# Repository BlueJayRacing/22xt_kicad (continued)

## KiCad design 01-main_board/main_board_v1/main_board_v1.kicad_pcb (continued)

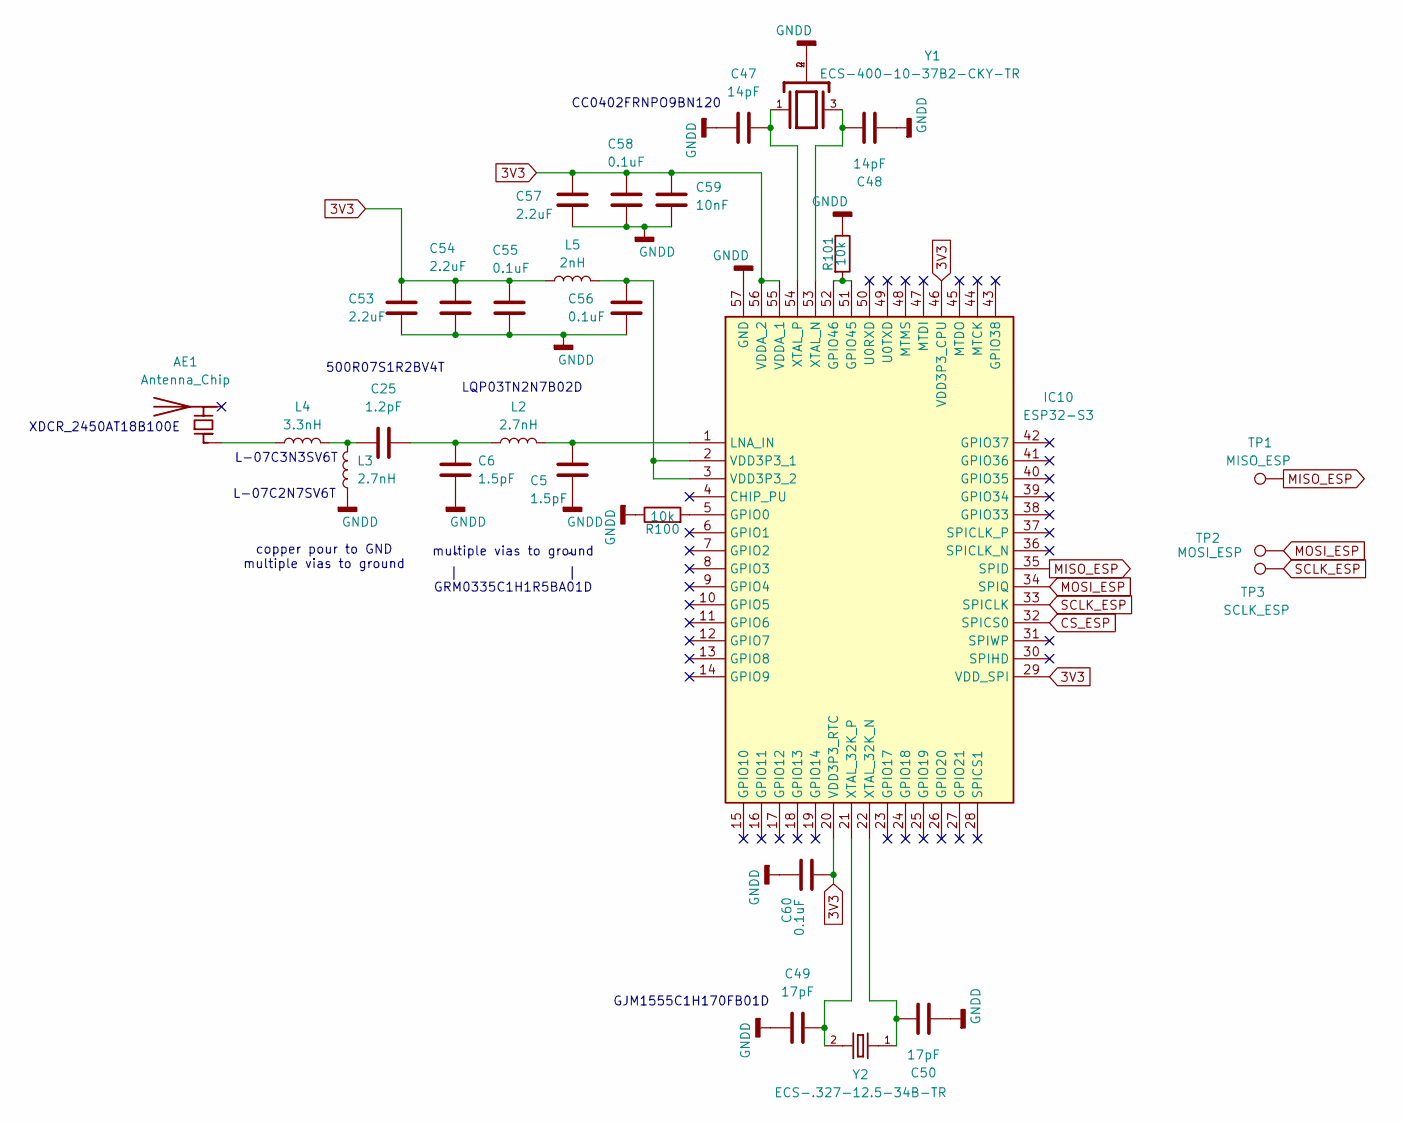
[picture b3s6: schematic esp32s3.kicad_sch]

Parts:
AE1: Antenna_Chip; XDCR_2450AT18B100E
C5, C6: 1.5pF; C_0603_1608Metric
C25: 1.2pF; C_0402_1005Metric
C47, C48: 14pF; C_0402_1005Metric
C49, C50: 17pF; C_0402_1005Metric
C53, C54, C57: 2.2uF; C_0402_1005Metric
C55, C56, C58, C60: 0.1uF; C_0402_1005Metric
C59: 10nF; C_0402_1005Metric
IC10: ESP32-S3; QFN40P700X700X90-57N-D; Mouser Part Number 356-ESP32-S3
L2: 2.7nH; L_0603_1608Metric
L3: 2.7nH; L_0402_1005Metric
L4: 3.3nH; L_0402_1005Metric
L5: 2nH; L_0402_1005Metric
R100, R101: 10k; R_0402_1005Metric
TP1: MISO_ESP; TestPoint_Pad_1.0x1.0mm
TP2: MOSI_ESP; TestPoint_Pad_1.0x1.0mm
TP3: SCLK_ESP; TestPoint_Pad_1.0x1.0mm
Y1: ECS-400-10-37B2-CKY-TR; XTAL_ECS-400-10-37B2-CKY-TR; PARTREV 2021
Y2: ECS-.327-12.5-34B-TR; XTAL_ECS-.327-12.5-34B-TR

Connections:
3V3: C53.1, C54.1, C55.1, C57.1, C58.1, C59.1, C60.1, IC10.20 (VDD3P3_RTC), IC10.29 (VDD_SPI), IC10.46 (VDD3P3_CPU), IC10.55 (VDDA_1), IC10.56 (VDDA_2), L5.1; also elsewhere on the board
CS_ESP: IC10.32 (SPICS0); also elsewhere on the board
MISO_ESP: IC10.35 (SPID), TP1.1; also elsewhere on the board
MOSI_ESP: IC10.34 (SPIQ), TP2.1; also elsewhere on the board
unnamed: AE1.1 (FEED), L4.1
unnamed: C25.1, L3.2, L4.2
unnamed: C6.1, C25.2, L2.1
unnamed: IC10.5 (GPIO0), R100.2
unnamed: IC10.51 (GPIO45), IC10.52 (GPIO46), R101.2
unnamed: C5.1, IC10.1 (LNA_IN), L2.2
unnamed: C56.1, IC10.2 (VDD3P3_1), IC10.3 (VDD3P3_2), L5.2
unnamed: C50.1, IC10.22 (XTAL_32K_N), Y2.1
unnamed: C49.1, IC10.21 (XTAL_32K_P), Y2.2
unnamed: C48.1, IC10.53 (XTAL_N), Y1.3
unnamed: C47.1, IC10.54 (XTAL_P), Y1.1
SCLK_ESP: IC10.33 (SPICLK), TP3.1; also elsewhere on the board

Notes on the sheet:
CC0402FRNPO9BN120
multiple vias to ground
500R07S1R2BV4T
L-07C3N3SV6T
L-07C2N7SV6T
LQP03TN2N7B02D
GJM1555C1H170FB01D
^ ^ | | GRM0335C1H1R5BA01D
XDCR_2450AT18B100E
copper pour to GND multiple vias to ground

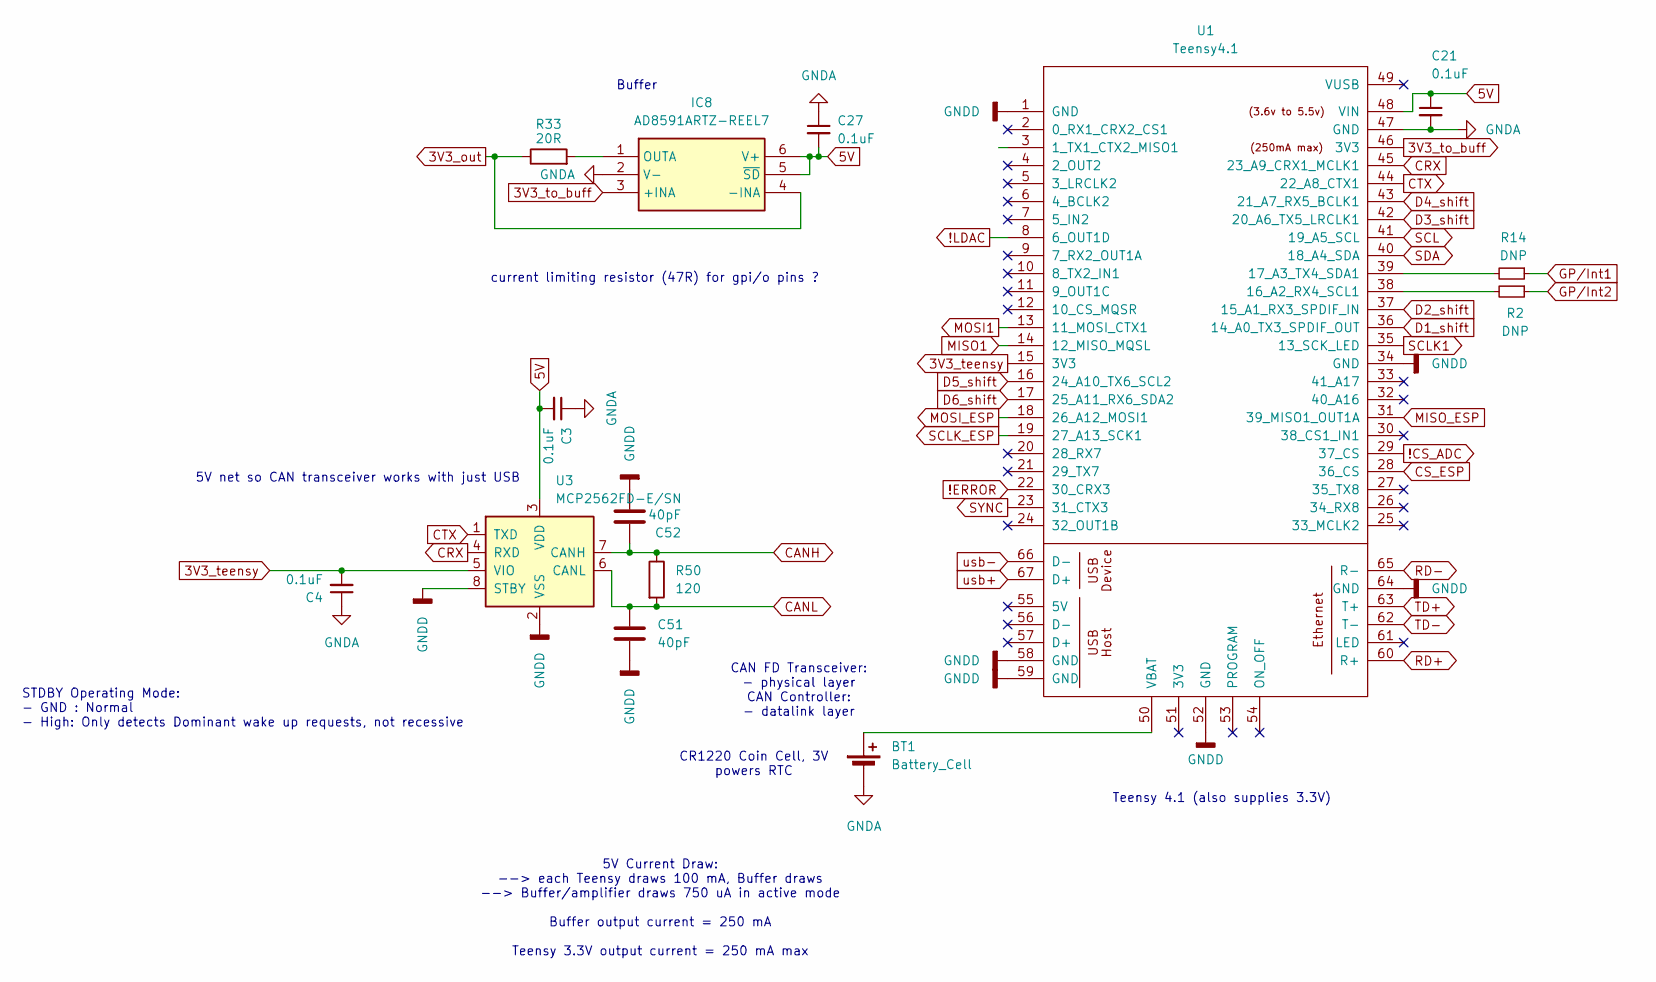
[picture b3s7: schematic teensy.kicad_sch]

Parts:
BT1: Battery_Cell; BatteryHolder_LINX_BAT-HLD-012-SMT
C3, C4, C21, C27: 0.1uF; C_0402_1005Metric
C51, C52: 40pF; C_0402_1005Metric
IC8: AD8591ARTZ-REEL7; SOT95P280X145-6N; Mouser Part Number 584-AD8591ARTZ-R7
R2, R14: DNP; R_0402_1005Metric
R33: 20R; R_0402_1005Metric
R50: 120; R_1206_3216Metric
U1: Teensy4.1; Teensy41
U3: MCP2562FD-E/SN; SOIC-8_3.9x4.9mm_P1.27mm

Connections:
3V3_out: IC8.4 (-INA), R33.1; also elsewhere on the board
3V3_teensy: C4.2, U1.15 (3V3), U3.5 (VIO); also elsewhere on the board
3V3_to_buff: IC8.3 (+INA), U1.46 (3V3)
5V: C3.2, C21.1, C27.2, IC8.5 (~SD), IC8.6 (V+), U1.48 (VIN), U3.3 (VDD); also elsewhere on the board
!CS_ADC: U1.29 (37_CS); also elsewhere on the board
!ERROR: U1.22 (30_CRX3); also elsewhere on the board
!LDAC: U1.8 (6_OUT1D); also elsewhere on the board
CANH: C52.1, R50.1, U3.7 (CANH); also elsewhere on the board
CANL: C51.1, R50.2, U3.6 (CANL); also elsewhere on the board
CRX: U1.45 (23_A9_CRX1_MCLK1), U3.4 (RXD)
CS_ESP: U1.28 (36_CS); also elsewhere on the board
CTX: U1.44 (22_A8_CTX1), U3.1 (TXD)
D1_shift: U1.36 (14_A0_TX3_SPDIF_OUT); also elsewhere on the board
D2_shift: U1.37 (15_A1_RX3_SPDIF_IN); also elsewhere on the board
D3_shift: U1.42 (20_A6_TX5_LRCLK1); also elsewhere on the board
D4_shift: U1.43 (21_A7_RX5_BCLK1); also elsewhere on the board
D5_shift: U1.16 (24_A10_TX6_SCL2); also elsewhere on the board
D6_shift: U1.17 (25_A11_RX6_SDA2); also elsewhere on the board
GP/Int1: R14.1; also elsewhere on the board
GP/Int2: R2.1; also elsewhere on the board
MISO1: U1.14 (12_MISO_MQSL); also elsewhere on the board
MISO_ESP: U1.31 (39_MISO1_OUT1A); also elsewhere on the board
MOSI1: U1.13 (11_MOSI_CTX1); also elsewhere on the board
MOSI_ESP: U1.18 (26_A12_MOSI1); also elsewhere on the board
unnamed: BT1.1 (+), U1.50 (VBAT)
unnamed: IC8.1 (OUTA), R33.2
unnamed: R2.2, U1.38 (16_A2_RX4_SCL1)
unnamed: R14.2, U1.39 (17_A3_TX4_SDA1)
RD+: U1.60 (R+); also elsewhere on the board
RD-: U1.65 (R-); also elsewhere on the board
SCL: U1.41 (19_A5_SCL); also elsewhere on the board
SCLK1: U1.35 (13_SCK_LED); also elsewhere on the board
SCLK_ESP: U1.19 (27_A13_SCK1); also elsewhere on the board
SDA: U1.40 (18_A4_SDA); also elsewhere on the board
SYNC: U1.23 (31_CTX3); also elsewhere on the board
TD+: U1.63 (T+); also elsewhere on the board
TD-: U1.62 (T-); also elsewhere on the board
usb+: U1.67 (D+); also elsewhere on the board
usb-: U1.66 (D-); also elsewhere on the board

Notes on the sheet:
Buffer
5V Current Draw: --> each Teensy draws 100 mA, Buffer draws --> Buffer/amplifier draws 750 uA in active mode Buffer output current = 250 mA Teensy 3.3V output current = 250 mA max
STDBY Operating Mode: - GND : Normal - High: Only detects Dominant wake up requests, not recessive
CR1220 Coin Cell, 3V powers RTC
Teensy 4.1 (also supplies 3.3V)
5V net so CAN transceiver works with just USB
CAN FD Transceiver: - physical layer CAN Controller: - datalink layer
current limiting resistor (47R) for gpi/o pins ?

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
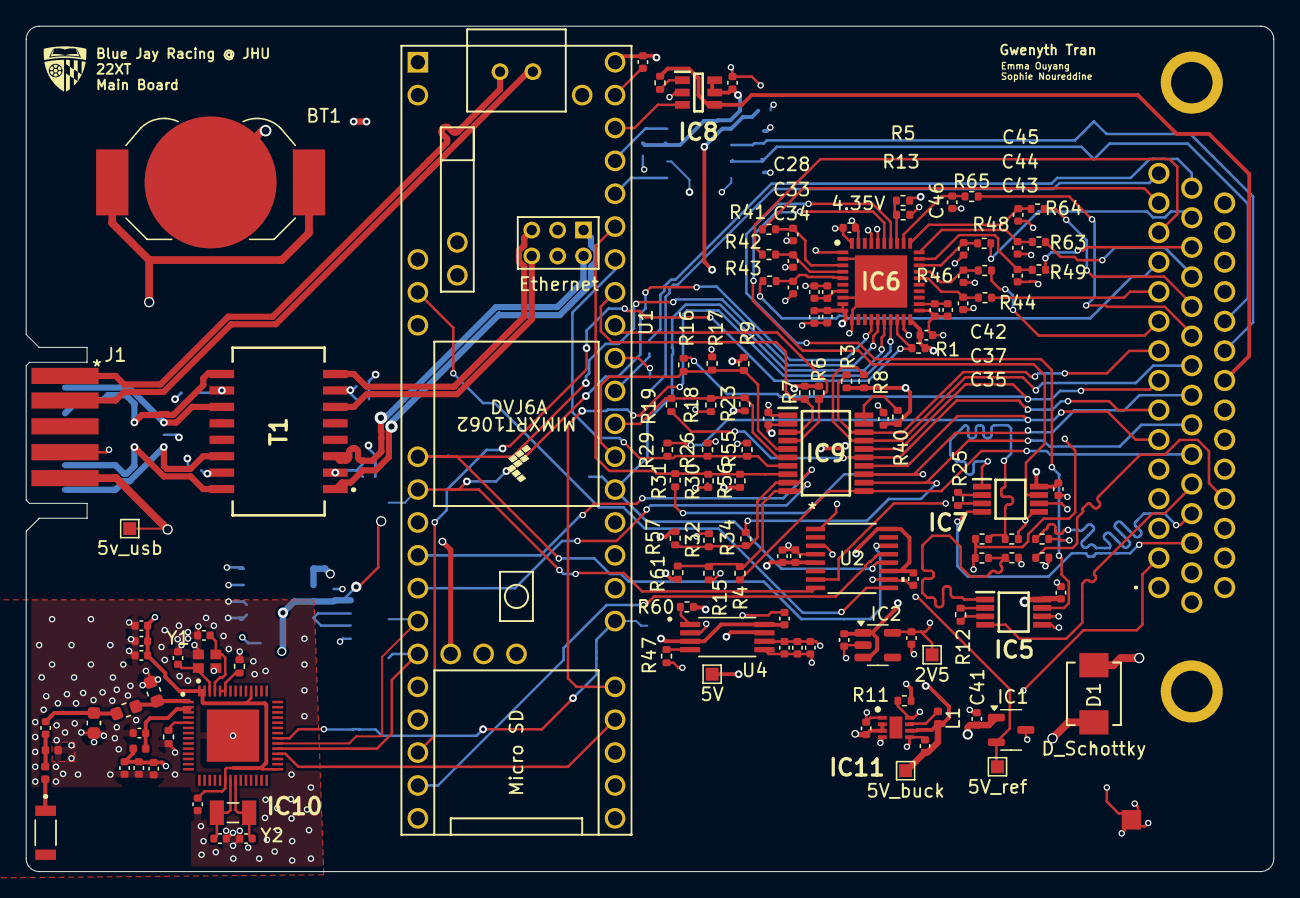
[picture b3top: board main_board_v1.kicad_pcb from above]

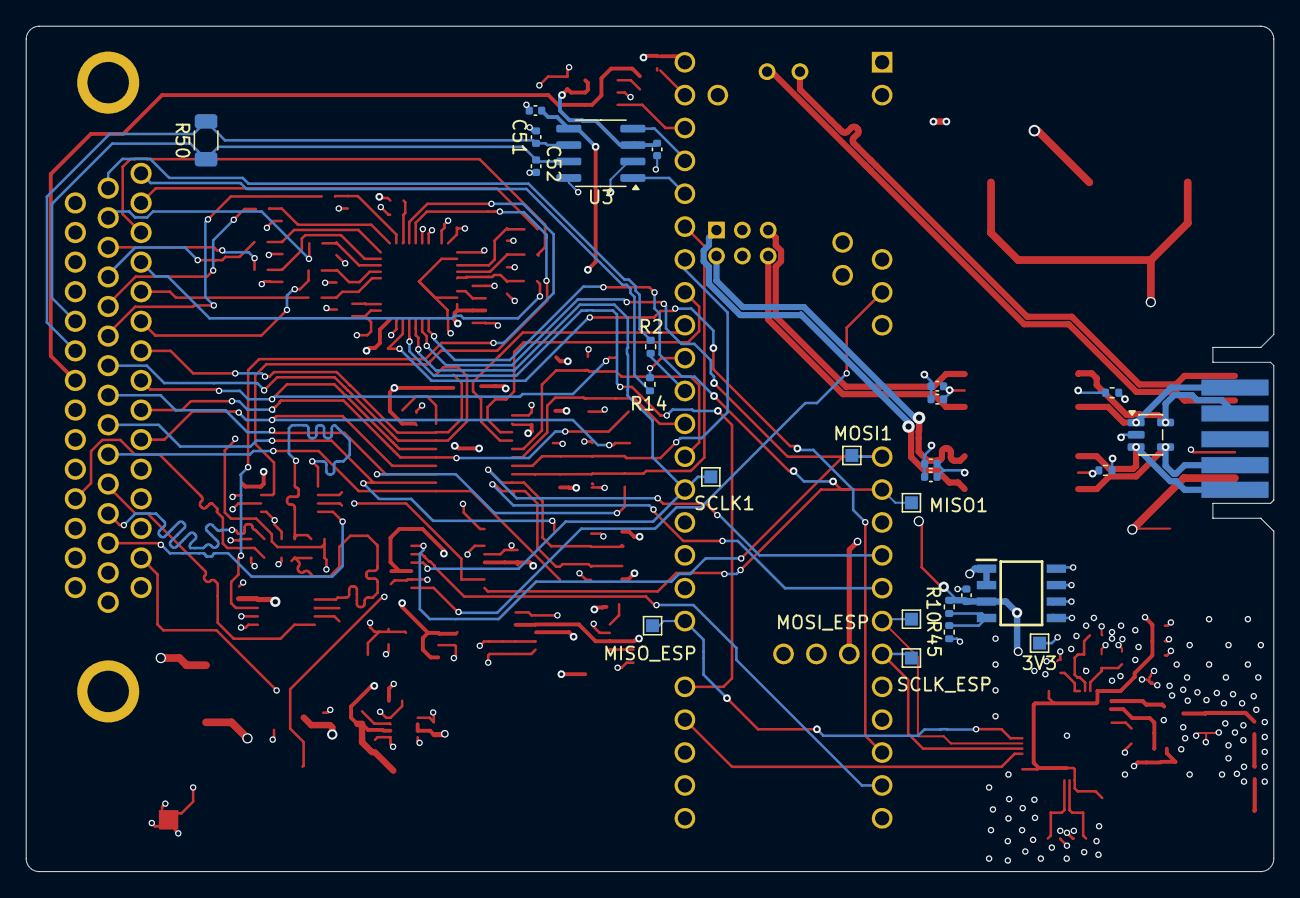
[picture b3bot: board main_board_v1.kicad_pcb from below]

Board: 4 copper layers, 96.4 x 65.3 mm, 159 parts (26 on the bottom side), 121 nets.

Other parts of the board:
5v_usb: 5V_usb; TestPoint_Pad_1.0x1.0mm

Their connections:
5V_usb: 5v_usb.1; also elsewhere on the board

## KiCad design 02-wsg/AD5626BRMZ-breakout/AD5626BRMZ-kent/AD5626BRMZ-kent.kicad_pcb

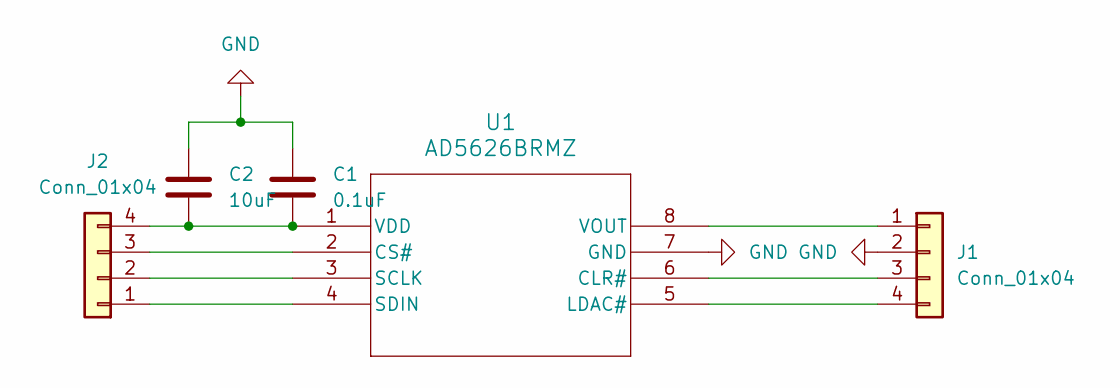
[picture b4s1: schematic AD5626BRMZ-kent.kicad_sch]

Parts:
C1: 0.1uF; C_0402_1005Metric
C2: 10uF; C_0603_1608Metric
J1, J2: Conn_01x04; PinHeader_1x04_P2.54mm_Vertical
U1: AD5626BRMZ; RM_8_ADI

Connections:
GND: C1.2, C2.2, J1.2, U1.7 (GND)
unnamed: J1.1, U1.8 (VOUT)
unnamed: J1.3, U1.6 (CLR#)
unnamed: J1.4, U1.5 (LDAC#)
unnamed: J2.1, U1.4 (SDIN)
unnamed: J2.2, U1.3 (SCLK)
unnamed: J2.3, U1.2 (CS#)
unnamed: C1.1, C2.1, J2.4, U1.1 (VDD)

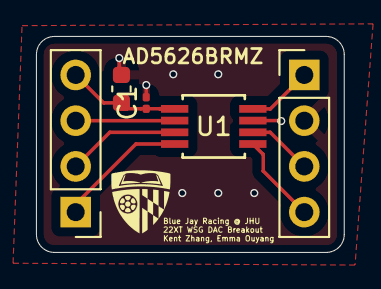
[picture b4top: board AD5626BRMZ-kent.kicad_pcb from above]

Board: 2 copper layers, 17.1 x 12.0 mm, 5 parts (0 on the bottom side), 8 nets.

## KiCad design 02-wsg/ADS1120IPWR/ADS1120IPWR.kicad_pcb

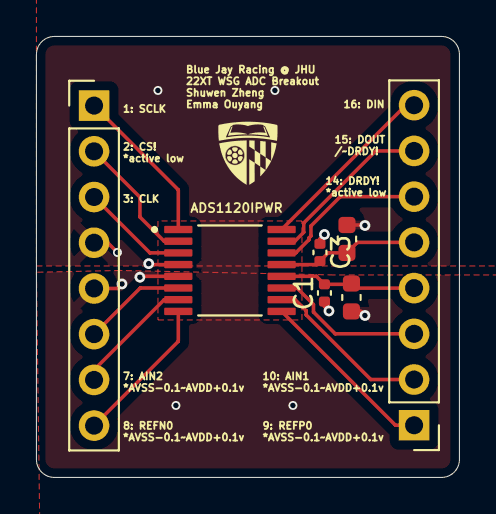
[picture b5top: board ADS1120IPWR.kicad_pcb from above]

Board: 2 copper layers, 23.5 x 24.5 mm, 7 parts (0 on the bottom side), 15 nets.

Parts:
C1, C3: 0.1 μF; C_0402_1005Metric
C2, C4: 10 μF; C_0603_1608Metric
J1, J2: Conn_01x08; PinHeader_1x08_P2.54mm_Vertical
U1: ADS1120IPWR; SOP65P640X120-16N

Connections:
AIN0/REFP1: J2.3, U1.11 (AIN0/REFP1)
AIN1: J2.2, U1.10 (AIN1)
AIN2: J1.7, U1.7 (AIN2)
AIN3/REFN1: J1.6, U1.6 (AIN3/REFN1)
AVDD: C1.2, C2.1, J2.4, U1.12 (AVDD)
CLK: J1.3, U1.3 (CLK)
CS!: J1.2, U1.2 (~CS)
DIN: J2.8, U1.16 (DIN)
DOUT: J2.7, U1.15 (DOUT/~DRDY)
DRDY!: J2.6, U1.14 (~DRDY)
DVDD: C3.2, C4.1, J2.5, U1.13 (DVDD)
GND: C1.1, C2.2, C3.1, C4.2, J1.4, J1.5, U1.4 (DGND), U1.5 (AVSS)
REFN0: J1.8, U1.8 (REFN0)
REFP0: J2.1, U1.9 (REFP0)
SCLK: J1.1, U1.1 (SCLK)
